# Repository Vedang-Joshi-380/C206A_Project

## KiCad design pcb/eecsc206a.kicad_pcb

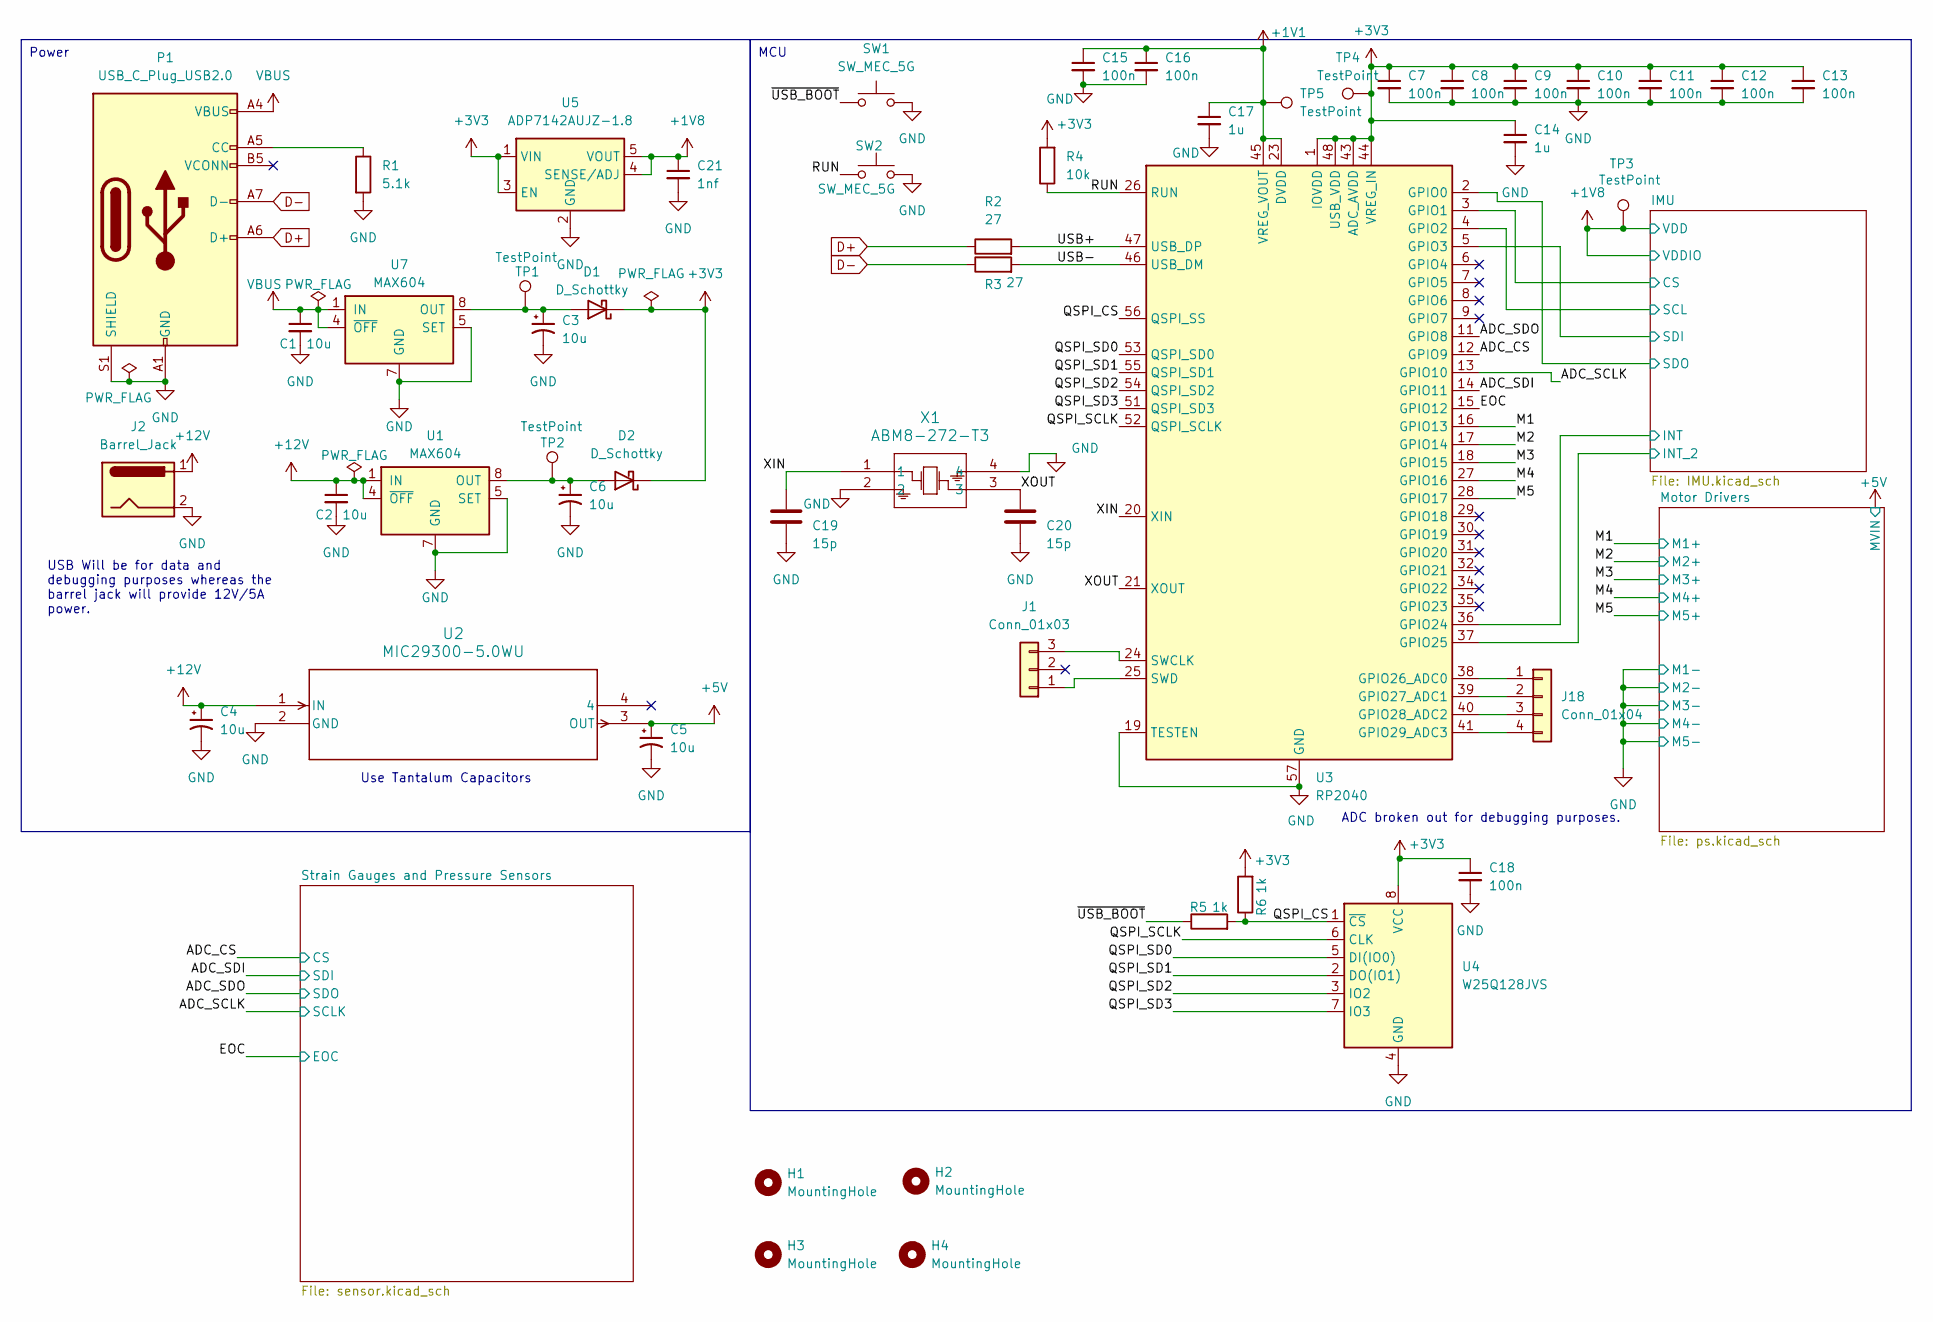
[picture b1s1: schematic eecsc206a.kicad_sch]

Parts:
C1, C2, C3, C6: 10u; C_0402_1005Metric
C4, C5: 10u; CP_EIA-3528-12_Kemet-T
C7, C8, C9, C10, C11, C12, C13, C15, C16, C18: 100n; C_0402_1005Metric
C14, C17: 1u; C_0402_1005Metric
C19, C20: 15p; C_0402_1005Metric
C21: 1nf; C_0402_1005Metric
D1, D2: D_Schottky; D_SOD-323F
H1, H2, H3, H4: MountingHole; MountingHole_3mm_Pad_Via
J1: Conn_01x03; PinHeader_1x03_P2.54mm_Vertical
J2: Barrel_Jack; BarrelJack_Wuerth_694106106102_2.0x5.5mm
J18: Conn_01x04; SolderWire-0.1sqmm_1x04_P3.6mm_D0.4mm_OD1mm
P1: USB_C_Plug_USB2.0; USB_C_Receptacle_Molex_105450-0101
R1: 5.1k; R_0402_1005Metric_Pad0.72x0.64mm_HandSolder
R2, R3: 27; R_0402_1005Metric_Pad0.72x0.64mm_HandSolder
R4: 10k; R_0402_1005Metric_Pad0.72x0.64mm_HandSolder
R5, R6: 1k; R_0402_1005Metric_Pad0.72x0.64mm_HandSolder
SW1, SW2: SW_MEC_5G; SW_SPST_FSMSM
TP1, TP2, TP3, TP4, TP5: TestPoint; TestPoint_Pad_D2.0mm
U1, U7: MAX604; PowerIntegrations_SO-8
U2: MIC29300-5.0WU; TO-263-3_MCL
U3: RP2040; QFN-56-1EP_7x7mm_P0.4mm_EP3.2x3.2mm
U4: W25Q128JVS; SOIC-8_5.23x5.23mm_P1.27mm
U5: ADP7142AUJZ-1.8; TSOT-23-5
X1: ABM8-272-T3; ABM8-272-T3_ABR

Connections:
+1V8: C21.1, TP3.1, U5.4 (SENSE/ADJ), U5.5 (VOUT); also elsewhere on the board
+3V3: C7.1, C8.1, C9.1, C10.1, C11.1, C12.1, C13.1, C14.1, C18.1, D1.1 (K), D2.1 (K), R4.2, R6.2, TP4.1, U3.1 (IOVDD), U3.10 (IOVDD), U3.22 (IOVDD), U3.33 (IOVDD), U3.42 (IOVDD), U3.43 (ADC_AVDD), U3.44 (VREG_IN), U3.48 (USB_VDD), U3.49 (IOVDD), U4.8 (VCC), U5.1 (VIN), U5.3 (EN); also elsewhere on the board
+5V: C5.1, U2.3 (OUT); also elsewhere on the board
+12V: C2.1, C4.1, J2.1, U1.1 (IN), U1.4 (~OFF), U2.1 (IN)
/ADC_CS: U3.12 (GPIO9); also elsewhere on the board
/ADC_SCLK: U3.13 (GPIO10); also elsewhere on the board
/ADC_SDI: U3.14 (GPIO11); also elsewhere on the board
/ADC_SDO: U3.11 (GPIO8); also elsewhere on the board
/EOC: U3.15 (GPIO12); also elsewhere on the board
/IMU/CS: U3.3 (GPIO1); also elsewhere on the board
/IMU/INT: U3.36 (GPIO24); also elsewhere on the board
/IMU/INT_2: U3.37 (GPIO25); also elsewhere on the board
/IMU/SCL: U3.4 (GPIO2); also elsewhere on the board
/IMU/SDI: U3.5 (GPIO3); also elsewhere on the board
/IMU/SDO: U3.2 (GPIO0); also elsewhere on the board
/M1: U3.16 (GPIO13); also elsewhere on the board
/M2: U3.17 (GPIO14); also elsewhere on the board
/M3: U3.18 (GPIO15); also elsewhere on the board
/M4: U3.27 (GPIO16); also elsewhere on the board
/M5: U3.28 (GPIO17); also elsewhere on the board
/QSPI_CS: R5.2, R6.1, U3.56 (QSPI_SS), U4.1 (~CS)
/QSPI_SCLK: U3.52 (QSPI_SCLK), U4.6 (CLK)
/QSPI_SD0: U3.53 (QSPI_SD0), U4.5 (DI(IO0))
/QSPI_SD1: U3.55 (QSPI_SD1), U4.2 (DO(IO1))
/QSPI_SD2: U3.54 (QSPI_SD2), U4.3 (IO2)
/QSPI_SD3: U3.51 (QSPI_SD3), U4.7 (IO3)
/USB+: R2.2, U3.47 (USB_DP)
/USB-: R3.2, U3.46 (USB_DM)
/XIN: C19.1, U3.20 (XIN), X1.1
/XOUT: C20.1, U3.21 (XOUT), X1.3
D+: P1.A6 (D+), R2.1
D-: P1.A7 (D-), R3.1
unnamed: C3.1, D1.2 (A), TP1.1, U7.8 (OUT)
unnamed: C6.1, D2.2 (A), TP2.1, U1.8 (OUT)
unnamed: J1.1, U3.25 (SWD)
unnamed: J1.3, U3.24 (SWCLK)
unnamed: J18.1, U3.38 (GPIO26_ADC0)
unnamed: J18.2, U3.39 (GPIO27_ADC1)
unnamed: J18.3, U3.40 (GPIO28_ADC2)
unnamed: J18.4, U3.41 (GPIO29_ADC3)
unnamed: P1.A5 (CC), R1.1
VBUS: C1.1, P1.A4 (VBUS), P1.A9 (VBUS), P1.B4 (VBUS), P1.B9 (VBUS), U7.1 (IN), U7.4 (~OFF)

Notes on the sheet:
USB Will be for data and debugging purposes whereas the barrel jack will provide 12V/5A power.
MCU
Power
ADC broken out for debugging purposes.
Use Tantalum Capacitors

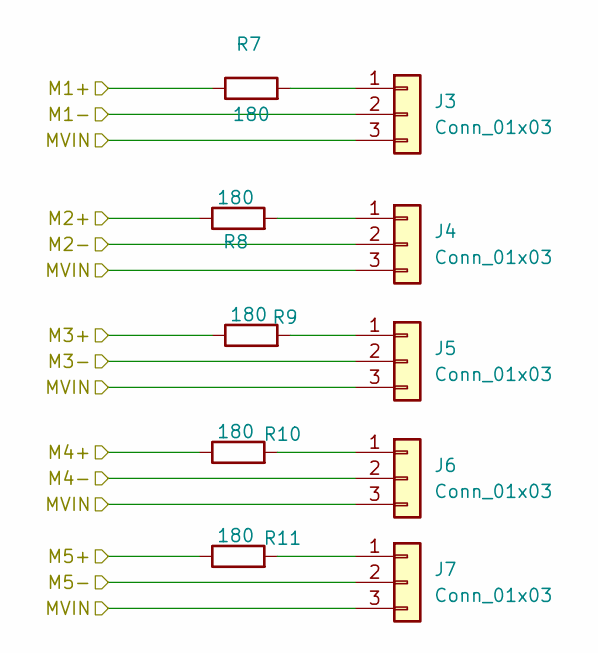
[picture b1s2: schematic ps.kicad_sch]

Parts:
J3, J4, J5, J6, J7: Conn_01x03; PinHeader_1x03_P2.54mm_Vertical
R7, R8, R9, R10, R11: 180; R_0402_1005Metric_Pad0.72x0.64mm_HandSolder

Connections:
+5V: J3.3, J4.3, J5.3, J6.3, J7.3; also elsewhere on the board
/M1: R7.1; also elsewhere on the board
/M2: R8.1; also elsewhere on the board
/M3: R9.1; also elsewhere on the board
/M4: R10.1; also elsewhere on the board
/M5: R11.1; also elsewhere on the board
unnamed: J3.1, R7.2
unnamed: J4.1, R8.2
unnamed: J5.1, R9.2
unnamed: J6.1, R10.2
unnamed: J7.1, R11.2

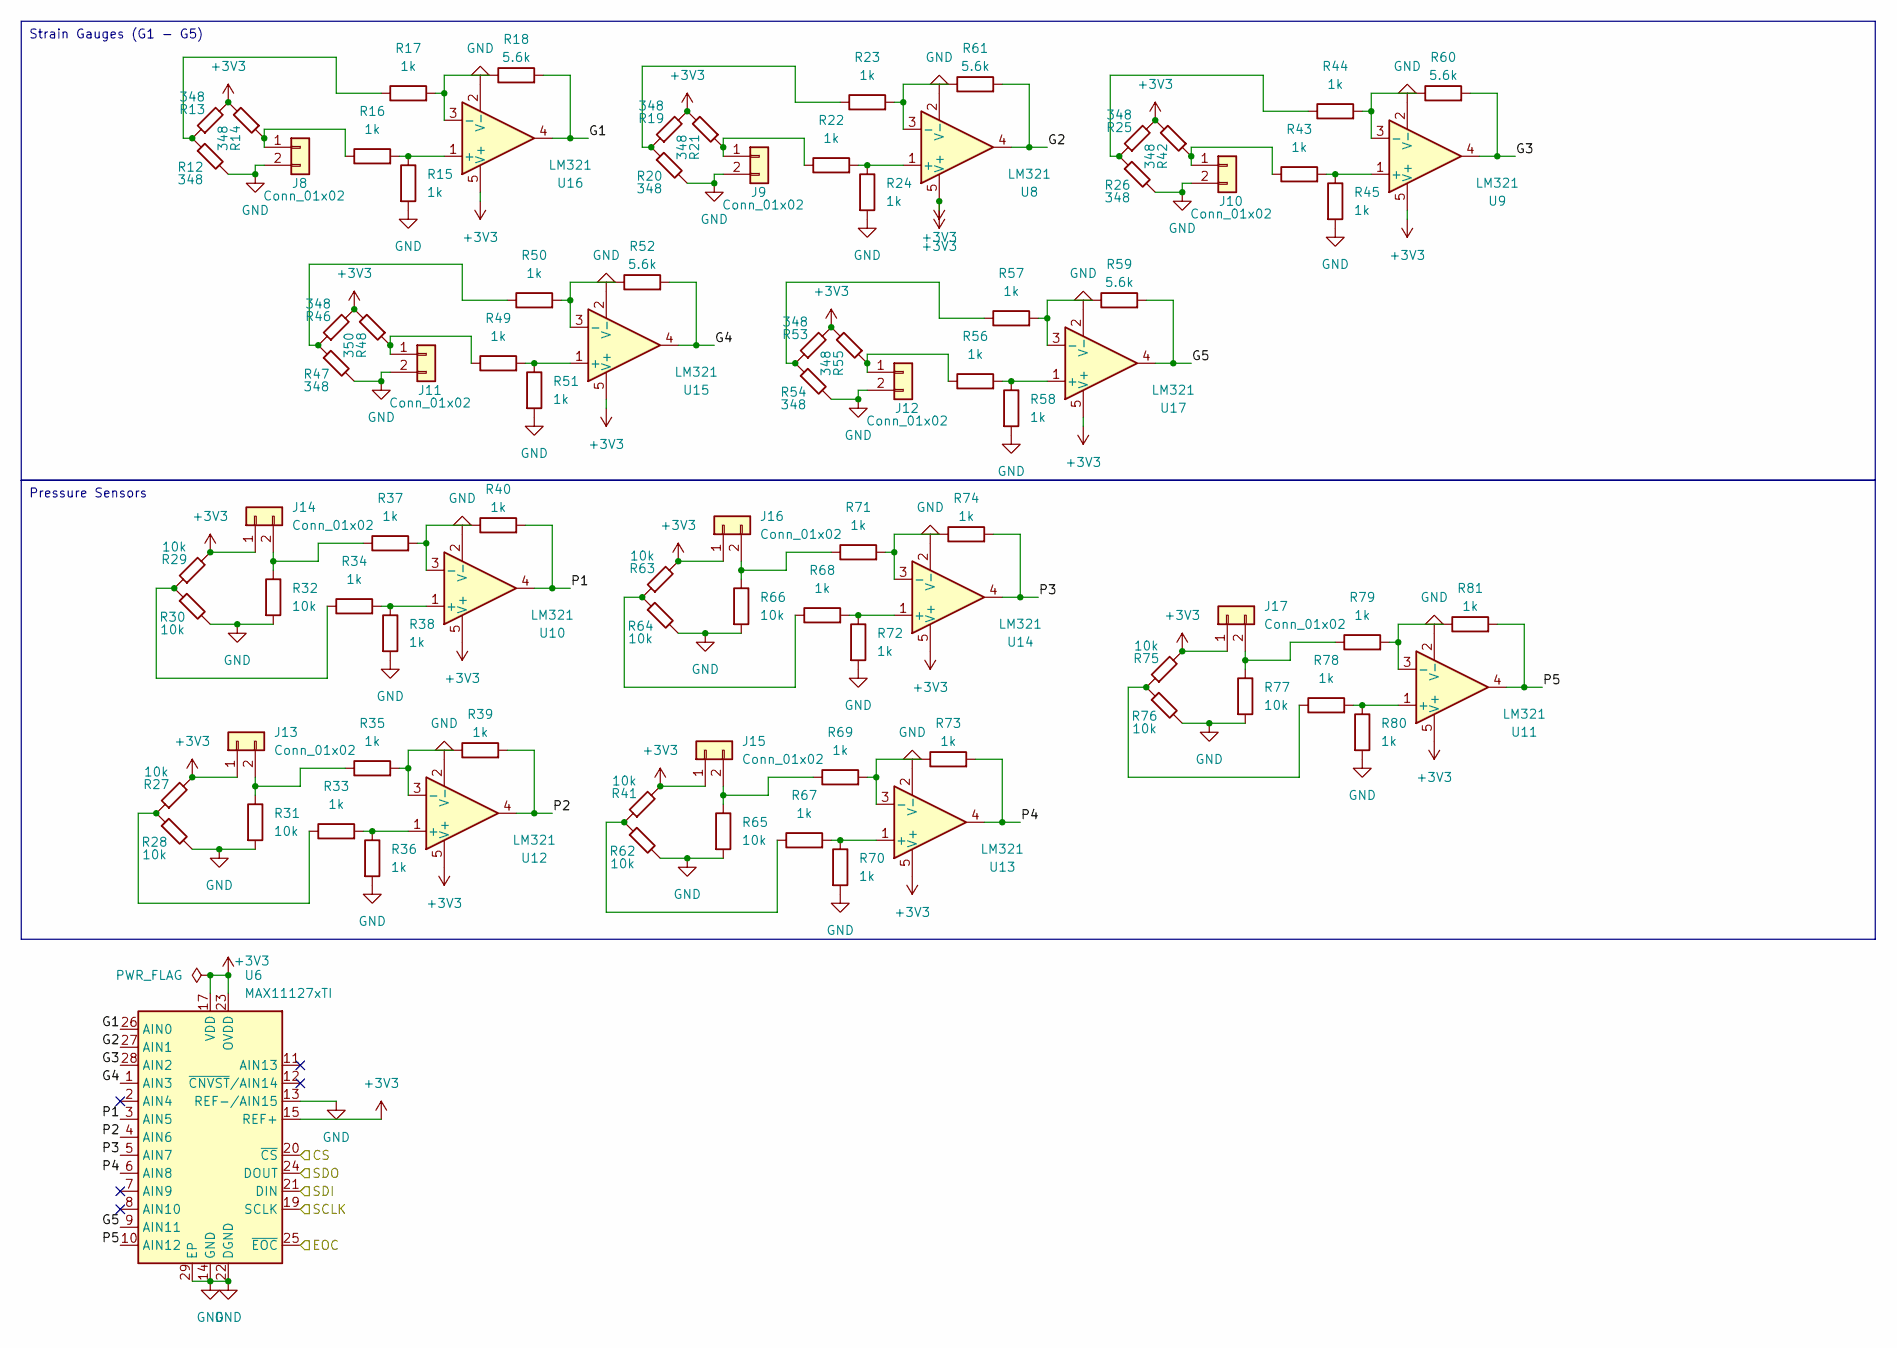
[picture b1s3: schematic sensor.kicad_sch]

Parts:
J8, J9, J10, J11, J12, J13, J14, J15, J16, J17: Conn_01x02; SolderWire-0.1sqmm_1x02_P3.6mm_D0.4mm_OD1mm
R12, R13, R14, R19, R20, R21, R25, R26, R42, R46, R47, R53, R54, R55: 348; R_0402_1005Metric_Pad0.72x0.64mm_HandSolder
R15, R16, R17, R22, R23, R24, R33, R34, R35, R36, R37, R38, R39, R40, R43, R44, R45, R49, R50, R51, R56, R57, R58, R67, R68, R69, R70, R71, R72, R73, R74, R78, R79, R80, R81: 1k; R_0402_1005Metric_Pad0.72x0.64mm_HandSolder
R18, R52, R59, R60, R61: 5.6k; R_0402_1005Metric_Pad0.72x0.64mm_HandSolder
R27, R28, R29, R30, R31, R32, R41, R62, R63, R64, R65, R66, R75, R76, R77: 10k; R_0402_1005Metric_Pad0.72x0.64mm_HandSolder
R48: 350; R_0402_1005Metric_Pad0.72x0.64mm_HandSolder
U6: MAX11127xTI; TQFN-28-1EP_5x5mm_P0.5mm_EP3.25x3.25mm
U8, U9, U10, U11, U12, U13, U14, U15, U16, U17: LM321; SOT-23-5

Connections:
+3V3: J13.1, J14.1, J15.1, J16.1, J17.1, R13.2, R14.2, R19.2, R21.2, R25.2, R27.2, R29.2, R41.2, R42.2, R46.2, R48.2, R53.2, R55.2, R63.2, R75.2, U6.15 (REF+), U6.17 (VDD), U6.18 (VDD), U6.23 (OVDD), U8.5 (V+), U9.5 (V+), U10.5 (V+), U11.5 (V+), U12.5 (V+), U13.5 (V+), U14.5 (V+), U15.5 (V+), U16.5 (V+), U17.5 (V+); also elsewhere on the board
/ADC_CS: U6.20 (~CS); also elsewhere on the board
/ADC_SCLK: U6.19 (SCLK); also elsewhere on the board
/ADC_SDI: U6.21 (DIN); also elsewhere on the board
/ADC_SDO: U6.24 (DOUT); also elsewhere on the board
/EOC: U6.25 (~EOC); also elsewhere on the board
/Strain Gauges and Pressure Sensors/G1: R18.2, U6.26 (AIN0), U16.4
/Strain Gauges and Pressure Sensors/G2: R61.2, U6.27 (AIN1), U8.4
/Strain Gauges and Pressure Sensors/G3: R60.2, U6.28 (AIN2), U9.4
/Strain Gauges and Pressure Sensors/G4: R52.2, U6.1 (AIN3), U15.4
/Strain Gauges and Pressure Sensors/G5: R59.2, U6.9 (AIN11), U17.4
/Strain Gauges and Pressure Sensors/P1: R40.2, U6.3 (AIN5), U10.4
/Strain Gauges and Pressure Sensors/P2: R39.2, U6.4 (AIN6), U12.4
/Strain Gauges and Pressure Sensors/P3: R74.2, U6.5 (AIN7), U14.4
/Strain Gauges and Pressure Sensors/P4: R73.2, U6.6 (AIN8), U13.4
/Strain Gauges and Pressure Sensors/P5: R81.2, U6.10 (AIN12), U11.4
unnamed: J8.1, R14.1, R16.1
unnamed: J9.1, R21.1, R22.1
unnamed: J10.1, R42.1, R43.1
unnamed: J11.1, R48.1, R49.1
unnamed: J12.1, R55.1, R56.1
unnamed: J13.2, R31.1, R35.1
unnamed: J14.2, R32.1, R37.1
unnamed: J15.2, R65.1, R69.1
unnamed: J16.2, R66.1, R71.1
unnamed: J17.2, R77.1, R79.1
unnamed: R12.1, R13.1, R17.1
unnamed: R19.1, R20.1, R23.1
unnamed: R25.1, R26.1, R44.1
unnamed: R27.1, R28.1, R33.1
unnamed: R29.1, R30.1, R34.1
unnamed: R41.1, R62.1, R67.1
unnamed: R46.1, R47.1, R50.1
unnamed: R53.1, R54.1, R57.1
unnamed: R63.1, R64.1, R68.1
unnamed: R75.1, R76.1, R78.1
unnamed: R22.2, R24.1, U8.1 (+)
unnamed: R23.2, R61.1, U8.3 (-)
unnamed: R43.2, R45.1, U9.1 (+)
unnamed: R44.2, R60.1, U9.3 (-)
unnamed: R34.2, R38.1, U10.1 (+)
unnamed: R37.2, R40.1, U10.3 (-)
unnamed: R78.2, R80.1, U11.1 (+)
unnamed: R79.2, R81.1, U11.3 (-)
unnamed: R33.2, R36.1, U12.1 (+)
unnamed: R35.2, R39.1, U12.3 (-)
unnamed: R67.2, R70.1, U13.1 (+)
unnamed: R69.2, R73.1, U13.3 (-)
unnamed: R68.2, R72.1, U14.1 (+)
unnamed: R71.2, R74.1, U14.3 (-)
unnamed: R49.2, R51.1, U15.1 (+)
unnamed: R50.2, R52.1, U15.3 (-)
unnamed: R15.1, R16.2, U16.1 (+)
unnamed: R17.2, R18.1, U16.3 (-)
unnamed: R56.2, R58.1, U17.1 (+)
unnamed: R57.2, R59.1, U17.3 (-)

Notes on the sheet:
Pressure Sensors
Strain Gauges (G1 - G5)

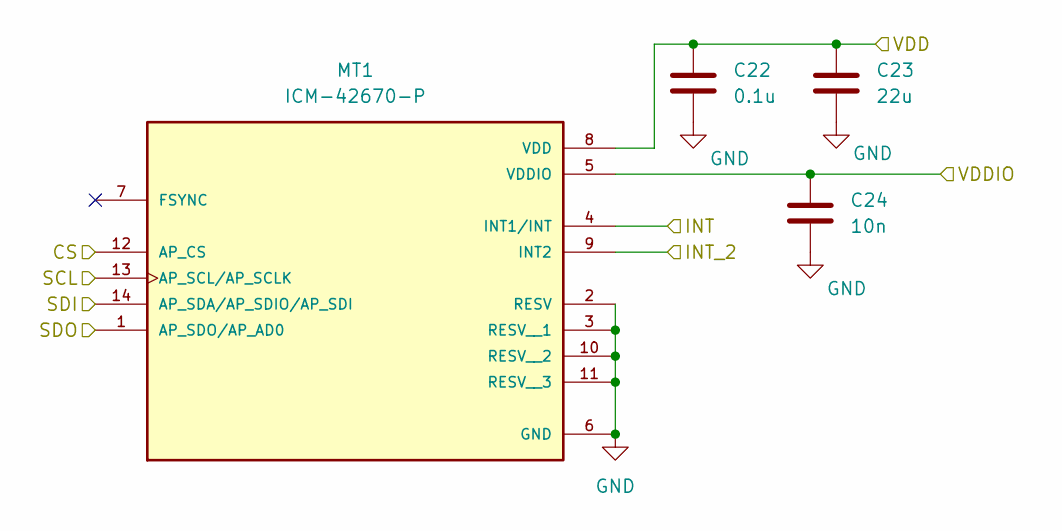
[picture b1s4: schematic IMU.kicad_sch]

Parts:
C22: 0.1u; C_0402_1005Metric
C23: 22u; C_0402_1005Metric
C24: 10n; C_0402_1005Metric
MT1: ICM-42670-P; PARTREV 1.1

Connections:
+1V8: C22.1, C23.1, C24.1, MT1.5 (VDDIO), MT1.8 (VDD); also elsewhere on the board
/IMU/CS: MT1.12 (AP_CS); also elsewhere on the board
/IMU/INT: MT1.4 (INT1/INT); also elsewhere on the board
/IMU/INT_2: MT1.9 (INT2); also elsewhere on the board
/IMU/SCL: MT1.13 (AP_SCL/AP_SCLK); also elsewhere on the board
/IMU/SDI: MT1.14 (AP_SDA/AP_SDIO/AP_SDI); also elsewhere on the board
/IMU/SDO: MT1.1 (AP_SDO/AP_AD0); also elsewhere on the board

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
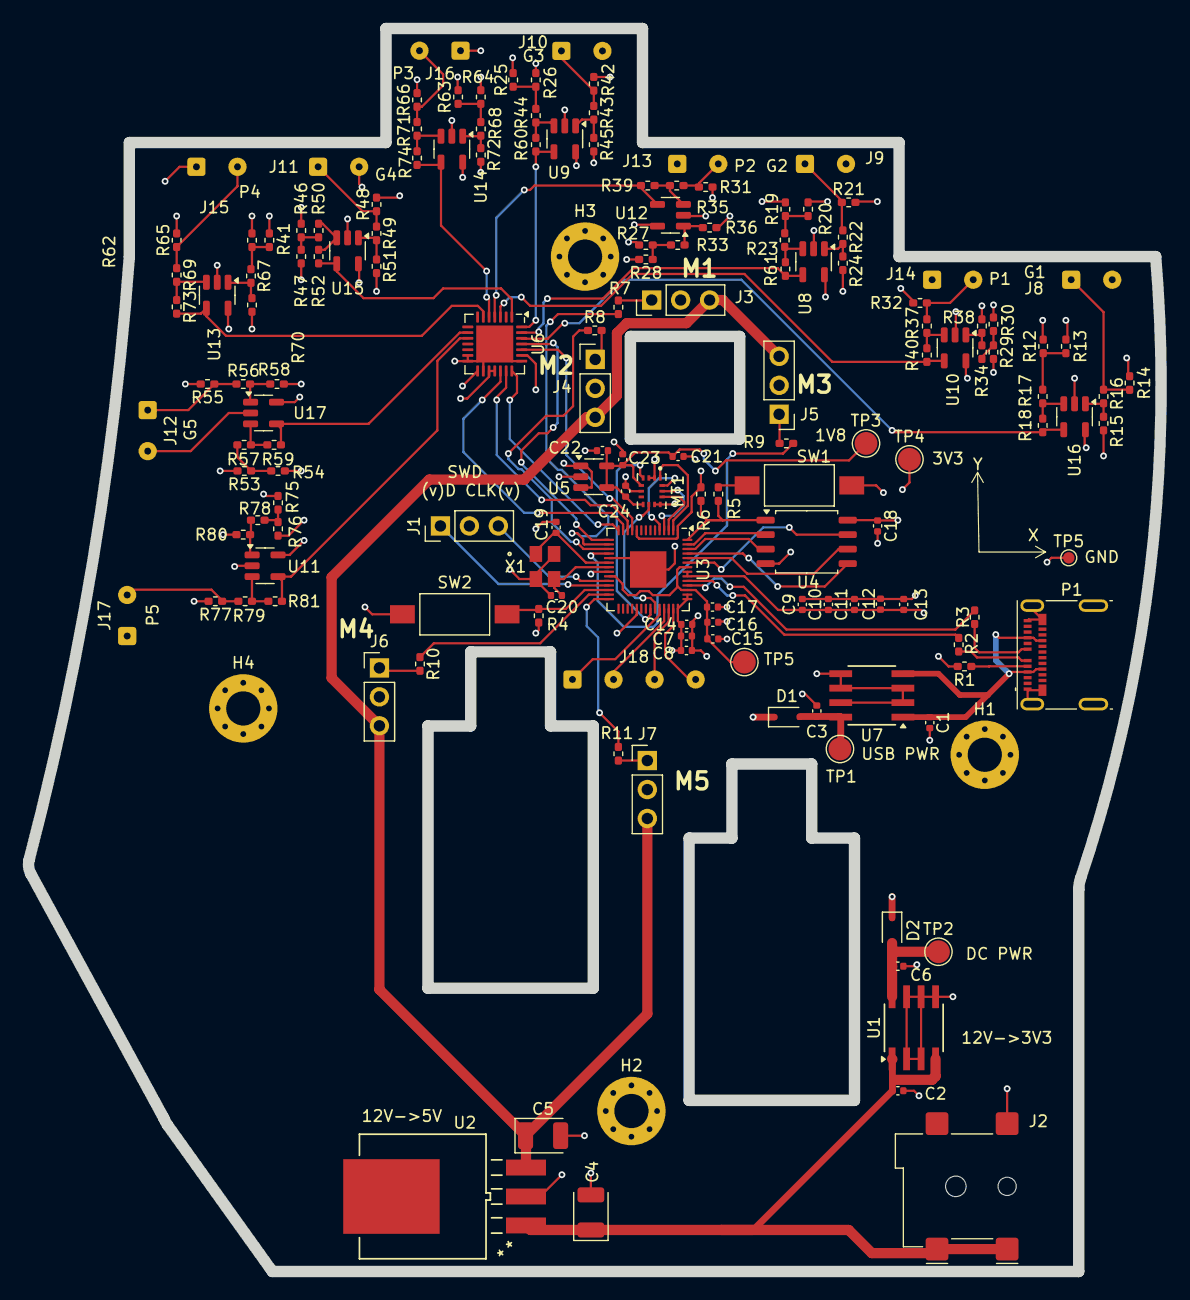
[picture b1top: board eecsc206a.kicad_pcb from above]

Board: 4 copper layers, 99.3 x 109.0 mm, 157 parts (0 on the bottom side), 101 nets.

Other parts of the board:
TP5#2: TestPoint; TestPoint_Pad_D2.0mm

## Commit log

2024-11-11 added lab7 and lab8 for reference files
2024-11-11 some progress with openpose but lacking build dependencies
2024-11-21 Added PCB to Git Repo
    Schematic is completed and ERC Clean.
2024-11-27 Camera image to joint angles
2024-11-27 Final PCB Design
2024-11-28 Made the PCB Manufacturable
    Oopsies
2024-12-10 Added rotation
2024-12-11 Pico servo code
2024-12-11 Late night checkpoint
2024-12-11 Fingers working
2024-12-11 Have everything but the arm movement working
2024-12-11 rosrc allows for the master uri to be set to the sawyer
2024-12-12 Everything works, moving to Alan
2024-12-12 Integration
2024-12-12 Renaming ik_cube.py to ik.py
2024-12-13 Improved grip
2024-12-17 added camera_pub.py to publish and updated joint_angles to work off single camera
